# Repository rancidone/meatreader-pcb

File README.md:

# ESP32 Wireless Thermometer

## Overview
This project is a **custom, battery-powered ESP32-based wireless thermometer** designed for BBQ and probe-based temperature monitoring.

The goal is to build a **robust, safe, and manufacturable device** suitable for real-world use, not a development board or a proof-of-concept. The design prioritizes reliability, serviceability, and clear engineering tradeoffs over extreme miniaturization or feature creep.

---

## Project Goals
- Battery-powered operation using a single-cell Li-ion / LiPo battery
- 24+ hour runtime under typical use
- In-place battery charging via USB-C (power only)
- Wireless connectivity (Wi-Fi required, BLE optional)
- OTA firmware update capability
- Support for multiple external thermistor probes
- Safe hot-plugging of all external connectors
- Outdoor and kitchen-safe electrical robustness
- Aluminum enclosure compatibility with minimal machining tools
- Low-cost, reproducible manufacturing
- Friendly to both SMT assembly and hand soldering

---

## Design Philosophy
This project is guided by the following principles:

- **Safety first**  
  All external connections must tolerate hot-plugging, static discharge, and user error without damaging the device.

- **Manufacturable by design**  
  Components and footprints are selected with real-world assembly in mind, favoring widely available parts and avoiding unnecessary complexity.

- **Debuggable and understandable**  
  The design should be easy to inspect, measure, and troubleshoot without specialized equipment.

- **Incremental improvement**  
  Revisions build on known-good designs, preserving proven circuits while improving specific areas as needed.

---

## Non-Goals
The following are explicitly out of scope:
- USB data or USB-PD support
- Power-bank or device-charging functionality
- Ultra-miniaturized or wearable form factors
- Dev-board style layouts
- Feature-driven complexity that compromises reliability

---

## Repository Structure
This repository contains the hardware design files and supporting documentation for the project.

Typical contents include:
- KiCad schematics and PCB layouts
- Project-local symbol and footprint libraries
- Design notes and revision history
- Manufacturing and assembly references

Generated outputs (Gerbers, fabrication files, temporary caches) are not tracked unless explicitly required.

---

## Status
This repository contains an evolving hardware design with multiple revisions. Earlier revisions serve as validated references; newer revisions focus on improved power handling, manufacturability, and long-term reliability.

---

## License
This project is intended for personal, educational, and hobbyist use. Licensing details may be added as the design matures.

---

## Acknowledgements
This project draws on common, well-established embedded hardware design patterns and prioritizes practical engineering over novelty.

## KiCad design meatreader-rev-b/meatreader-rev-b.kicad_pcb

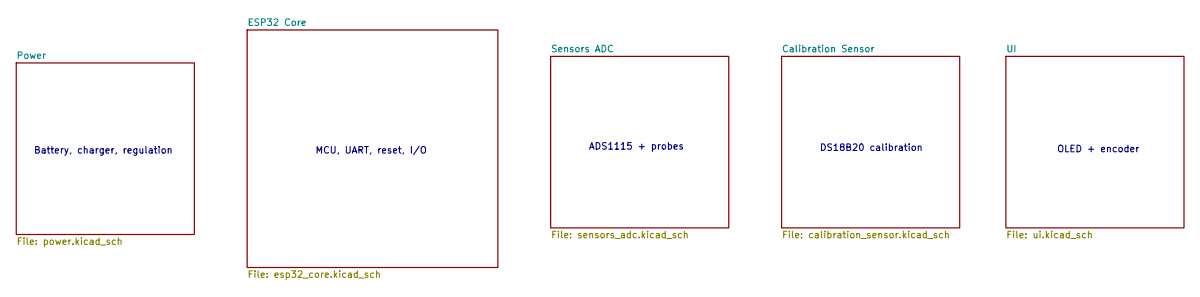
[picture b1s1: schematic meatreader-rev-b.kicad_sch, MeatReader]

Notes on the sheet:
MCU, UART, reset, I/O
ADS1115 + probes
OLED + encoder
Battery, charger, regulation
DS18B20 calibration

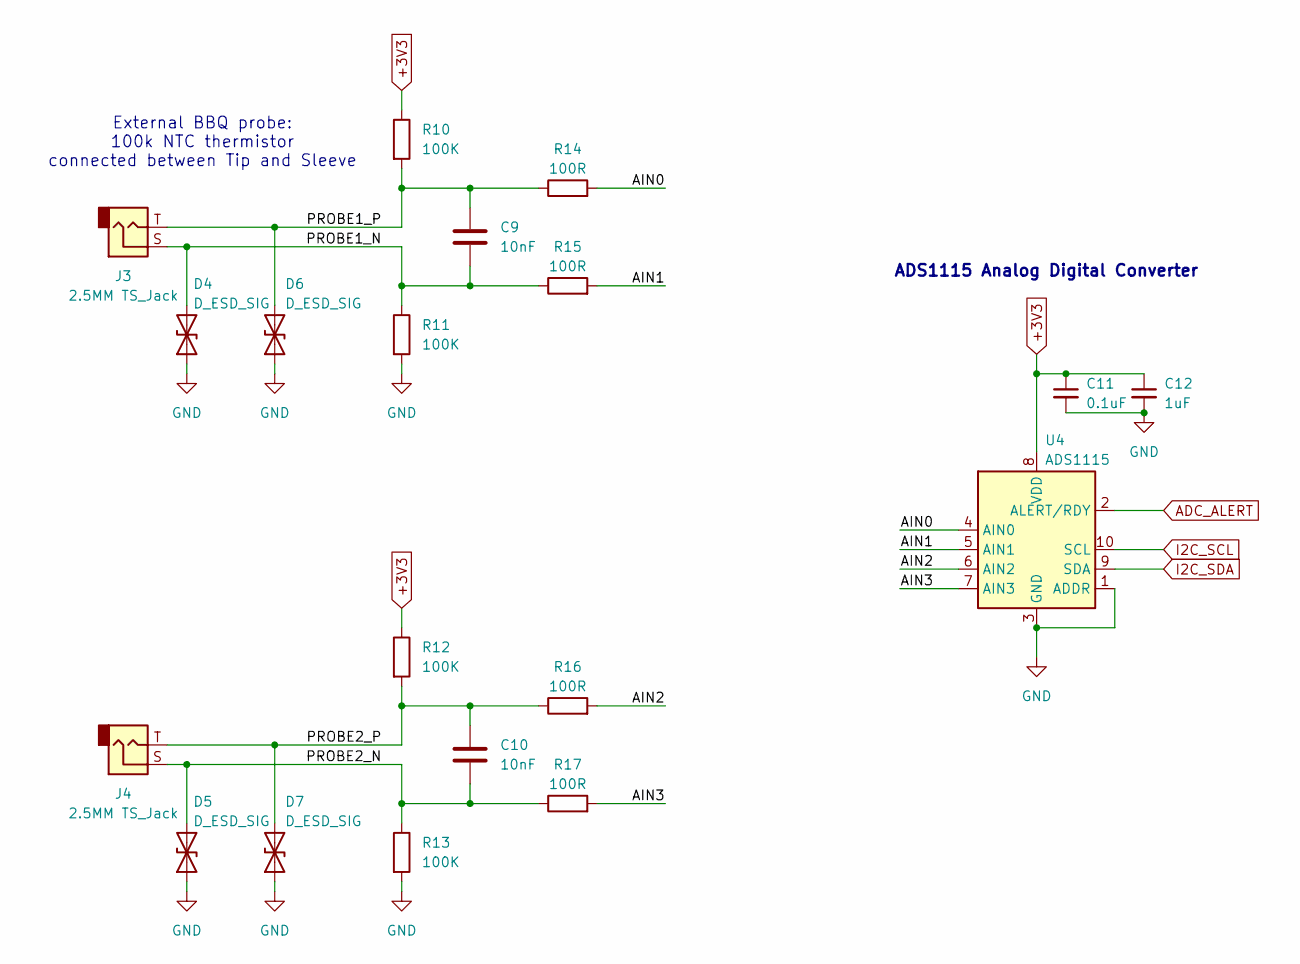
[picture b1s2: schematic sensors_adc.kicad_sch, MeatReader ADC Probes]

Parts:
C9, C10: 10nF; C_0603_1608Metric
C11: 0.1uF; C_0603_1608Metric
C12: 1uF; C_0603_1608Metric
D4, D5: D_ESD_SIG; D_0402_1005Metric; LCSC C20615778
D6, D7: D_ESD_SIG; D_0402_1005Metric
J3, J4: 2.5MM TS_Jack; Jack_2.5MM_PJ210B_TS; JLC_3DModel_Q 9e36057968d7478ca8658f227985305d
R10, R11, R12, R13: 100K; R_0603_1608Metric
R14, R15, R16, R17: 100R; R_0603_1608Metric
U4: ADS1115; TSSOP-10_3x3mm_P0.5mm

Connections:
+3V3: C11.1, C12.1, R10.1, R12.1, U4.8 (VDD); also elsewhere on the board
/Sensors ADC/AIN0: R14.2, U4.4 (AIN0)
/Sensors ADC/AIN1: R15.2, U4.5 (AIN1)
/Sensors ADC/AIN2: R16.2, U4.6 (AIN2)
/Sensors ADC/AIN3: R17.2, U4.7 (AIN3)
/Sensors ADC/PROBE1_N: C9.2, D4.2 (A2), J3.S, R11.1, R15.1
/Sensors ADC/PROBE1_P: C9.1, D6.2 (A2), J3.T, R10.2, R14.1
/Sensors ADC/PROBE2_N: C10.2, D5.2 (A2), J4.S, R13.1, R17.1
/Sensors ADC/PROBE2_P: C10.1, D7.2 (A2), J4.T, R12.2, R16.1
ADC_ALERT: U4.2 (ALERT/RDY); also elsewhere on the board
GND: C11.2, C12.2, D4.1 (A1), D5.1 (A1), D6.1 (A1), D7.1 (A1), R11.2, R13.2, U4.1 (ADDR), U4.3 (GND); also elsewhere on the board
I2C_SCL: U4.10 (SCL); also elsewhere on the board
I2C_SDA: U4.9 (SDA); also elsewhere on the board

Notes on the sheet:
External BBQ probe: 100k NTC thermistor connected between Tip and Sleeve
ADS1115 Analog Digital Converter

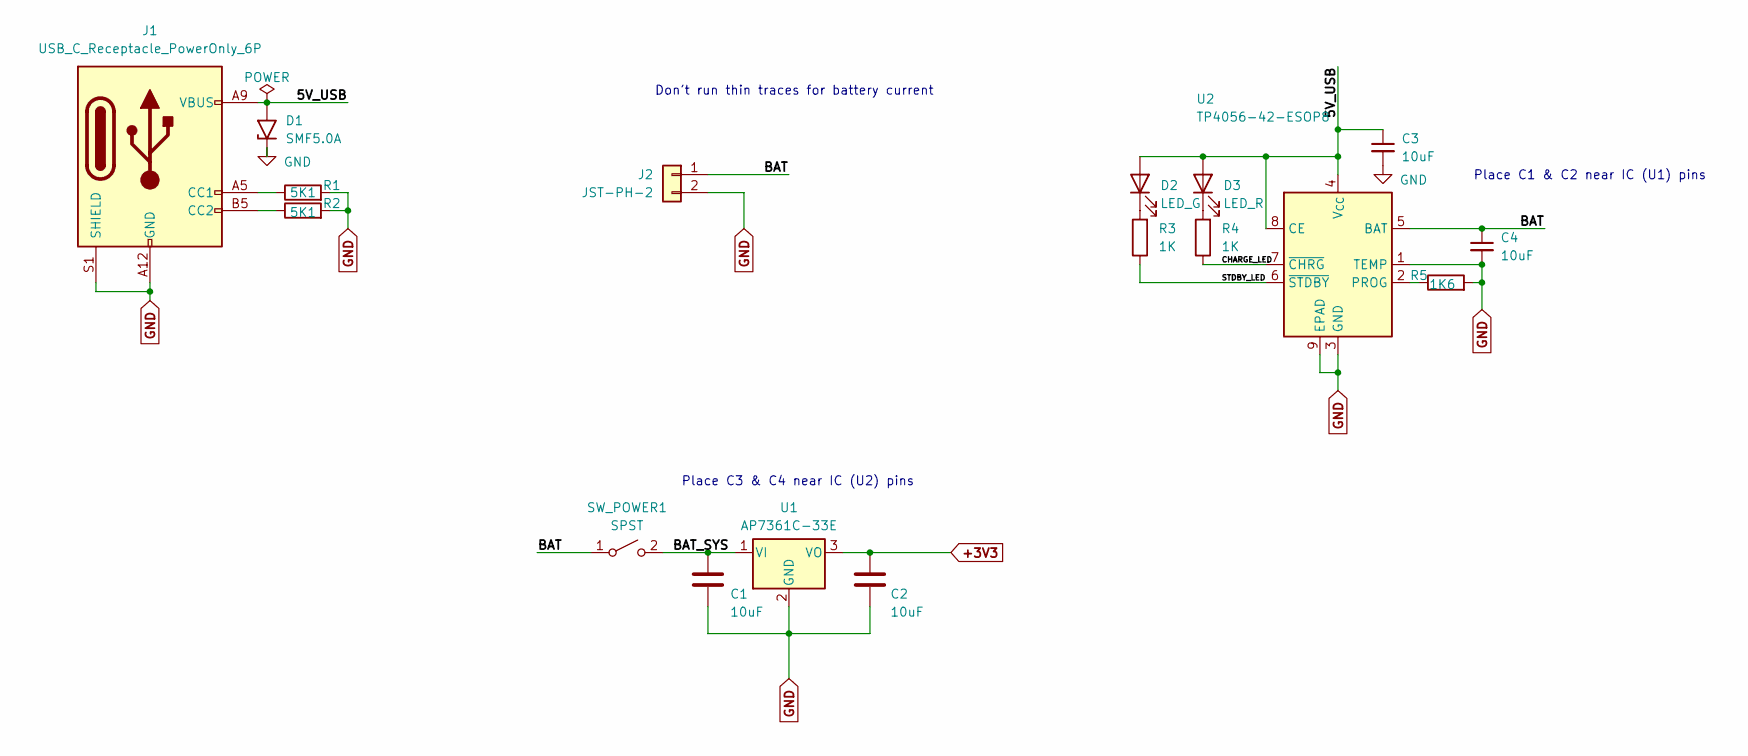
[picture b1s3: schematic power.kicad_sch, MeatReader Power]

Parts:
C1, C2, C3, C4: 10uF; C_0805_2012Metric
D1: SMF5.0A; D_SMF; LCSC C19077497
D2: LED_G; LED_D3.0mm
D3: LED_R; LED_D3.0mm
J1: USB_C_Receptacle_PowerOnly_6P; USB_C_Receptacle_HRO_TYPE-C-31-M-12
J2: JST-PH-2; JST_PH_B2B-PH-K_1x02_P2.00mm_Vertical
R1, R2: 5K1; R_0402_1005Metric
R3, R4: 1K; R_0402_1005Metric; LCSC C11702
R5: 1K6; R_0402_1005Metric
SW_POWER1: SPST; PinHeader_1x02_P2.54mm_Vertical
U1: AP7361C-33E; SOT-223-3_TabPin2
U2: TP4056-42-ESOP8; SOIC-8-1EP_3.9x4.9mm_P1.27mm_EP2.41x3.3mm

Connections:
+3V3: C2.1, U1.3 (VO); also elsewhere on the board
/Power/5V_USB: C3.1, D1.2 (A2), D2.2 (A), D3.2 (A), J1.A9 (VBUS), J1.B9 (VBUS), U2.4 (V_{CC}), U2.8 (CE)
/Power/BAT: C4.1, J2.1, SW_POWER1.1 (A), U2.5 (BAT)
/Power/BAT_SYS: C1.1, SW_POWER1.2 (B), U1.1 (VI)
/Power/CHARGE_LED: R4.1, U2.7 (~CHRG)
/Power/STDBY_LED: R3.1, U2.6 (~STDBY)
GND: C1.2, C2.2, C3.2, C4.2, D1.1 (A1), J1.A12 (GND), J1.B12 (GND), J1.S1 (SHIELD), J2.2, R1.2, R2.2, R5.2, U1.2 (GND), U2.1 (TEMP), U2.3 (GND), U2.9 (EPAD); also elsewhere on the board
unnamed: D2.1 (K), R3.2
unnamed: D3.1 (K), R4.2
unnamed: J1.A5 (CC1), R1.1
unnamed: J1.B5 (CC2), R2.1
unnamed: R5.1, U2.2 (PROG)

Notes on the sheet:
Don't run thin traces for battery current
Place C1 & C2 near IC (U1) pins
Place C3 & C4 near IC (U2) pins

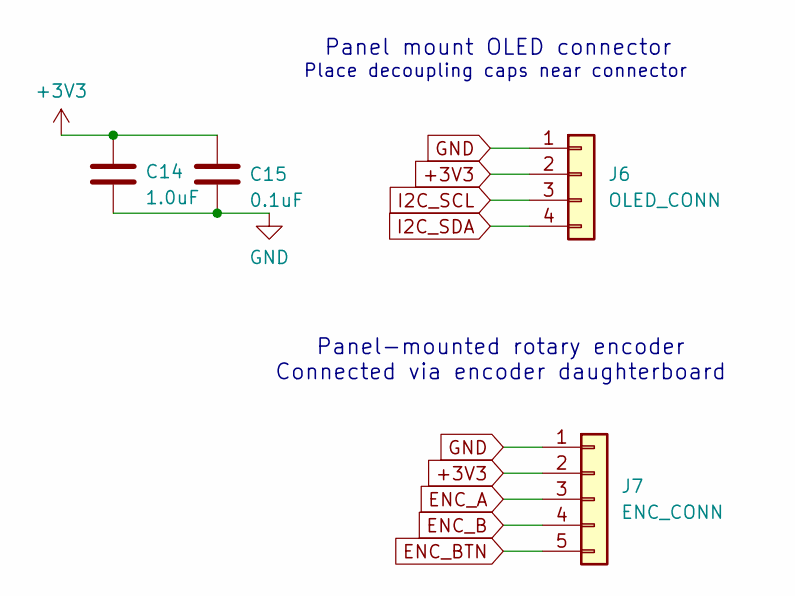
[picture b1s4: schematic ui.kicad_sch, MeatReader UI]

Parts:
C14: 1.0uF; C_0603_1608Metric
C15: 0.1uF; C_0603_1608Metric
J6: OLED_CONN; JST_XH_B4B-XH-AM_1x04_P2.50mm_Vertical
J7: ENC_CONN; JST_XH_B5B-XH-AM_1x05_P2.50mm_Vertical

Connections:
+3V3: C14.1, C15.1, J6.2, J7.2; also elsewhere on the board
ENC_A: J7.3; also elsewhere on the board
ENC_B: J7.4; also elsewhere on the board
ENC_BTN: J7.5; also elsewhere on the board
GND: C14.2, C15.2, J6.1, J7.1; also elsewhere on the board
I2C_SCL: J6.3; also elsewhere on the board
I2C_SDA: J6.4; also elsewhere on the board

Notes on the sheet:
Panel-mounted rotary encoder Connected via encoder daughterboard
Place decoupling caps near connector
Panel mount OLED connector

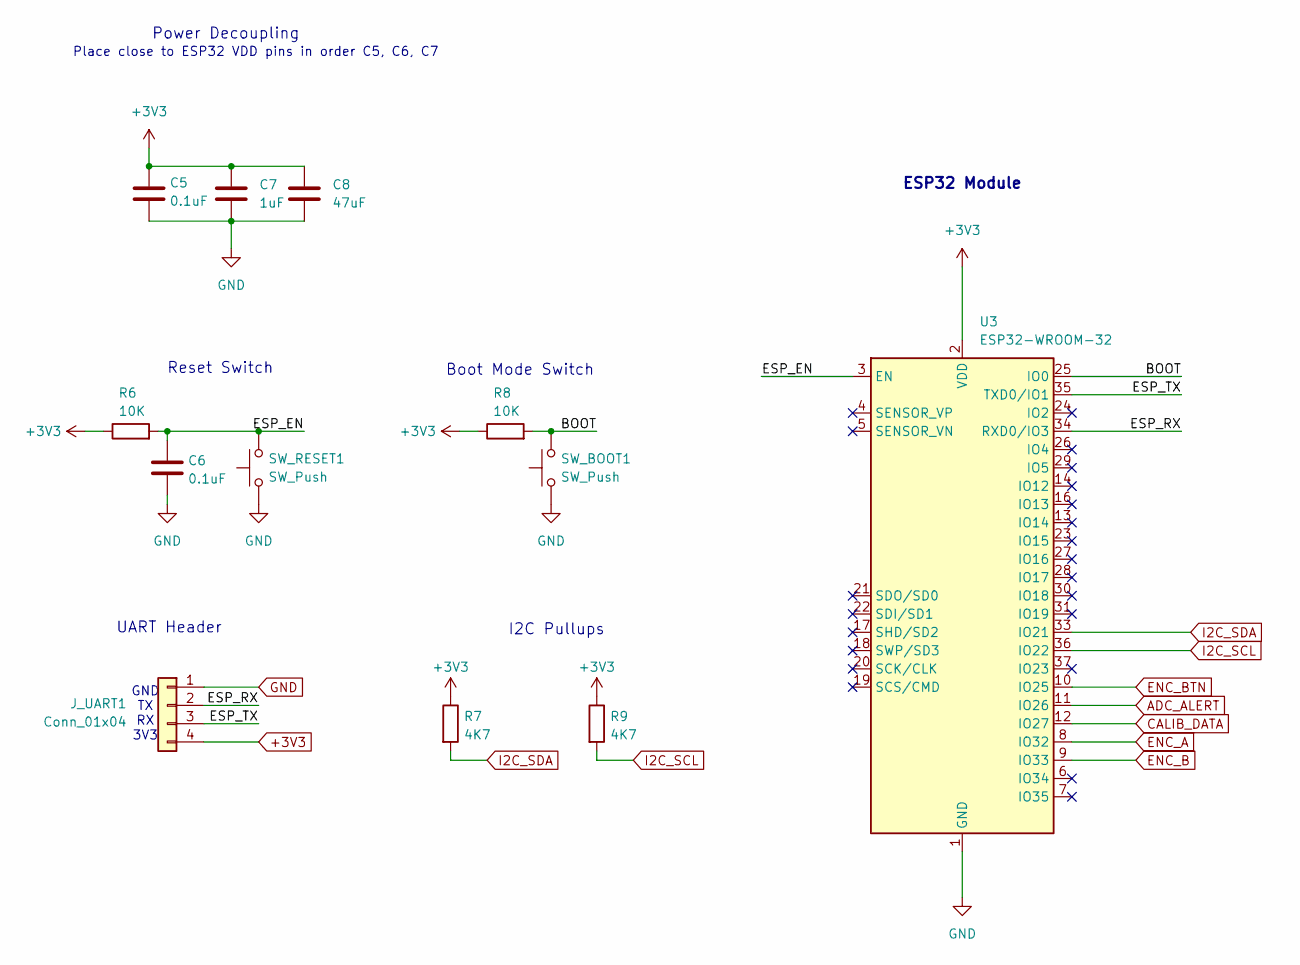
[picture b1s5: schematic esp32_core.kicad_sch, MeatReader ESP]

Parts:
C5, C6: 0.1uF; C_0603_1608Metric
C7: 1uF; C_0603_1608Metric
C8: 47uF; C_0805_2012Metric
J_UART1: Conn_01x04; PinHeader_1x04_P2.54mm_Vertical
R6, R8: 10K; R_0603_1608Metric
R7, R9: 4K7; R_0603_1608Metric
SW_BOOT1: SW_Push; Test_01x02
SW_RESET1: SW_Push; SW_PUSH_6mm
U3: ESP32-WROOM-32; ESP32-WROOM-32_NoThermals

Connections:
+3V3: C5.1, C7.1, C8.1, J_UART1.4, R6.1, R7.1, R8.1, R9.1, U3.2 (VDD); also elsewhere on the board
/ESP32 Core/BOOT: R8.2, SW_BOOT1.2, U3.25 (IO0)
/ESP32 Core/ESP_EN: C6.1, R6.2, SW_RESET1.2, U3.3 (EN)
/ESP32 Core/ESP_RX: J_UART1.2, U3.34 (RXD0/IO3)
/ESP32 Core/ESP_TX: J_UART1.3, U3.35 (TXD0/IO1)
ADC_ALERT: U3.11 (IO26); also elsewhere on the board
CALIB_DATA: U3.12 (IO27); also elsewhere on the board
ENC_A: U3.8 (IO32); also elsewhere on the board
ENC_B: U3.9 (IO33); also elsewhere on the board
ENC_BTN: U3.10 (IO25); also elsewhere on the board
GND: C5.2, C6.2, C7.2, C8.2, J_UART1.1, SW_BOOT1.1, SW_RESET1.1, U3.1 (GND), U3.15 (GND), U3.38 (GND), U3.39 (GND); also elsewhere on the board
I2C_SCL: R9.2, U3.36 (IO22); also elsewhere on the board
I2C_SDA: R7.2, U3.33 (IO21); also elsewhere on the board

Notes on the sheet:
GND TX RX 3V3
I2C Pullups
UART Header
Power Decoupling
Place close to ESP32 VDD pins in order C5, C6, C7
Reset Switch
Boot Mode Switch
ESP32 Module

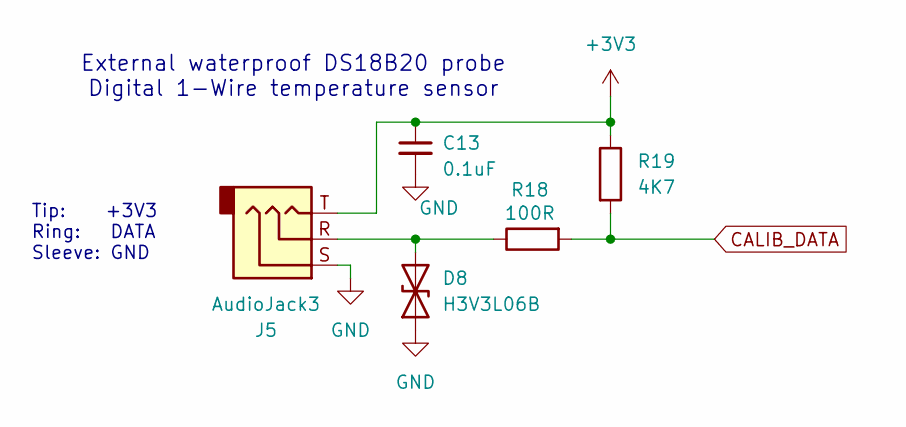
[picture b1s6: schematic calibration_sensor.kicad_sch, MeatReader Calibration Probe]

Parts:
C13: 0.1uF; C_0603_1608Metric
D8: H3V3L06B; D_0402_1005Metric
J5: AudioJack3; PJ-320A_TRS
R18: 100R; R_0603_1608Metric
R19: 4K7; R_0603_1608Metric

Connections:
+3V3: C13.1, J5.T, R19.1; also elsewhere on the board
CALIB_DATA: R18.2, R19.2; also elsewhere on the board
GND: C13.2, D8.1 (A1), J5.S; also elsewhere on the board
unnamed: D8.2 (A2), J5.R, R18.1

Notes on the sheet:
External waterproof DS18B20 probe Digital 1-Wire temperature sensor
Tip: +3V3 Ring: DATA Sleeve: GND

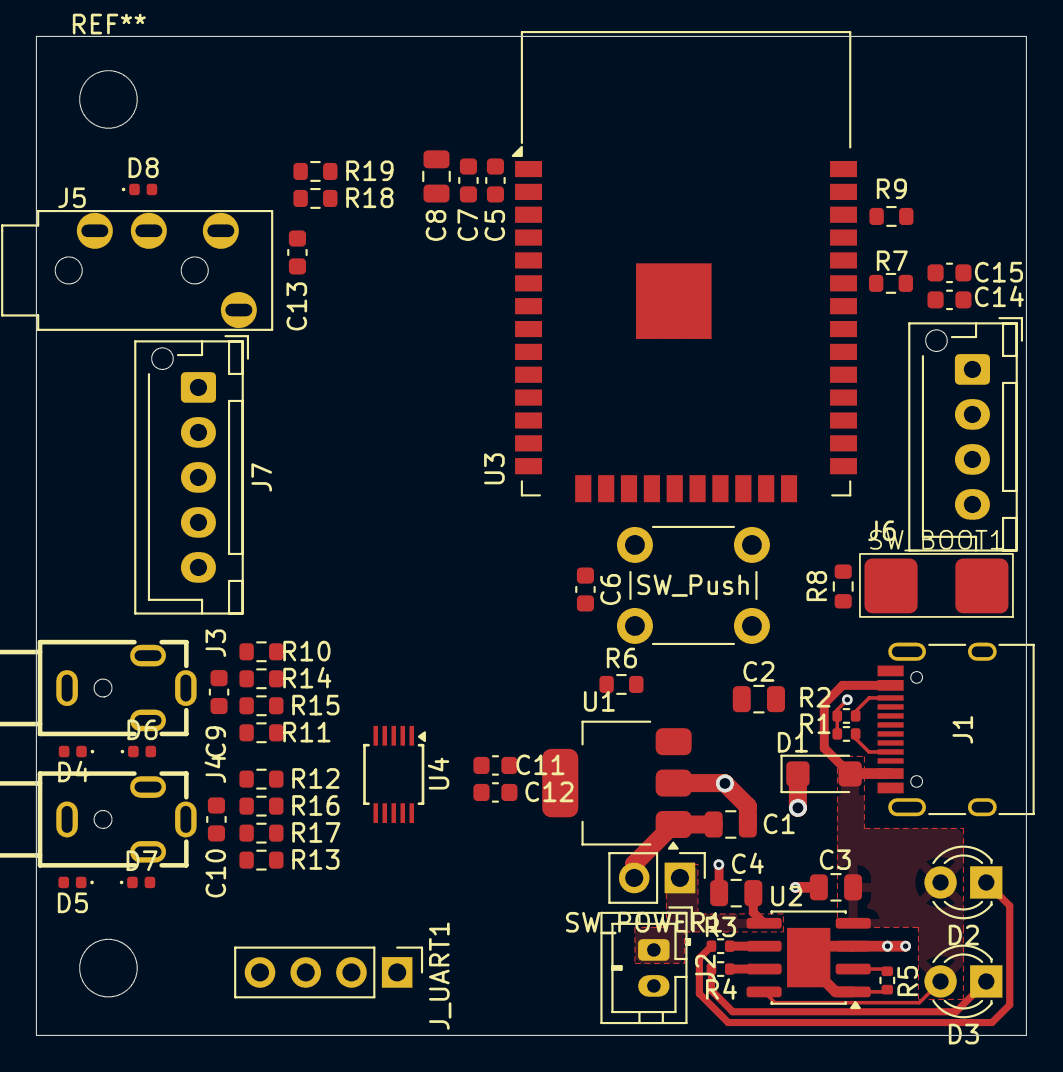
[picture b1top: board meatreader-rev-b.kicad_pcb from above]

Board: 2 copper layers, 55.0 x 55.5 mm, 57 parts (0 on the bottom side), 32 nets.

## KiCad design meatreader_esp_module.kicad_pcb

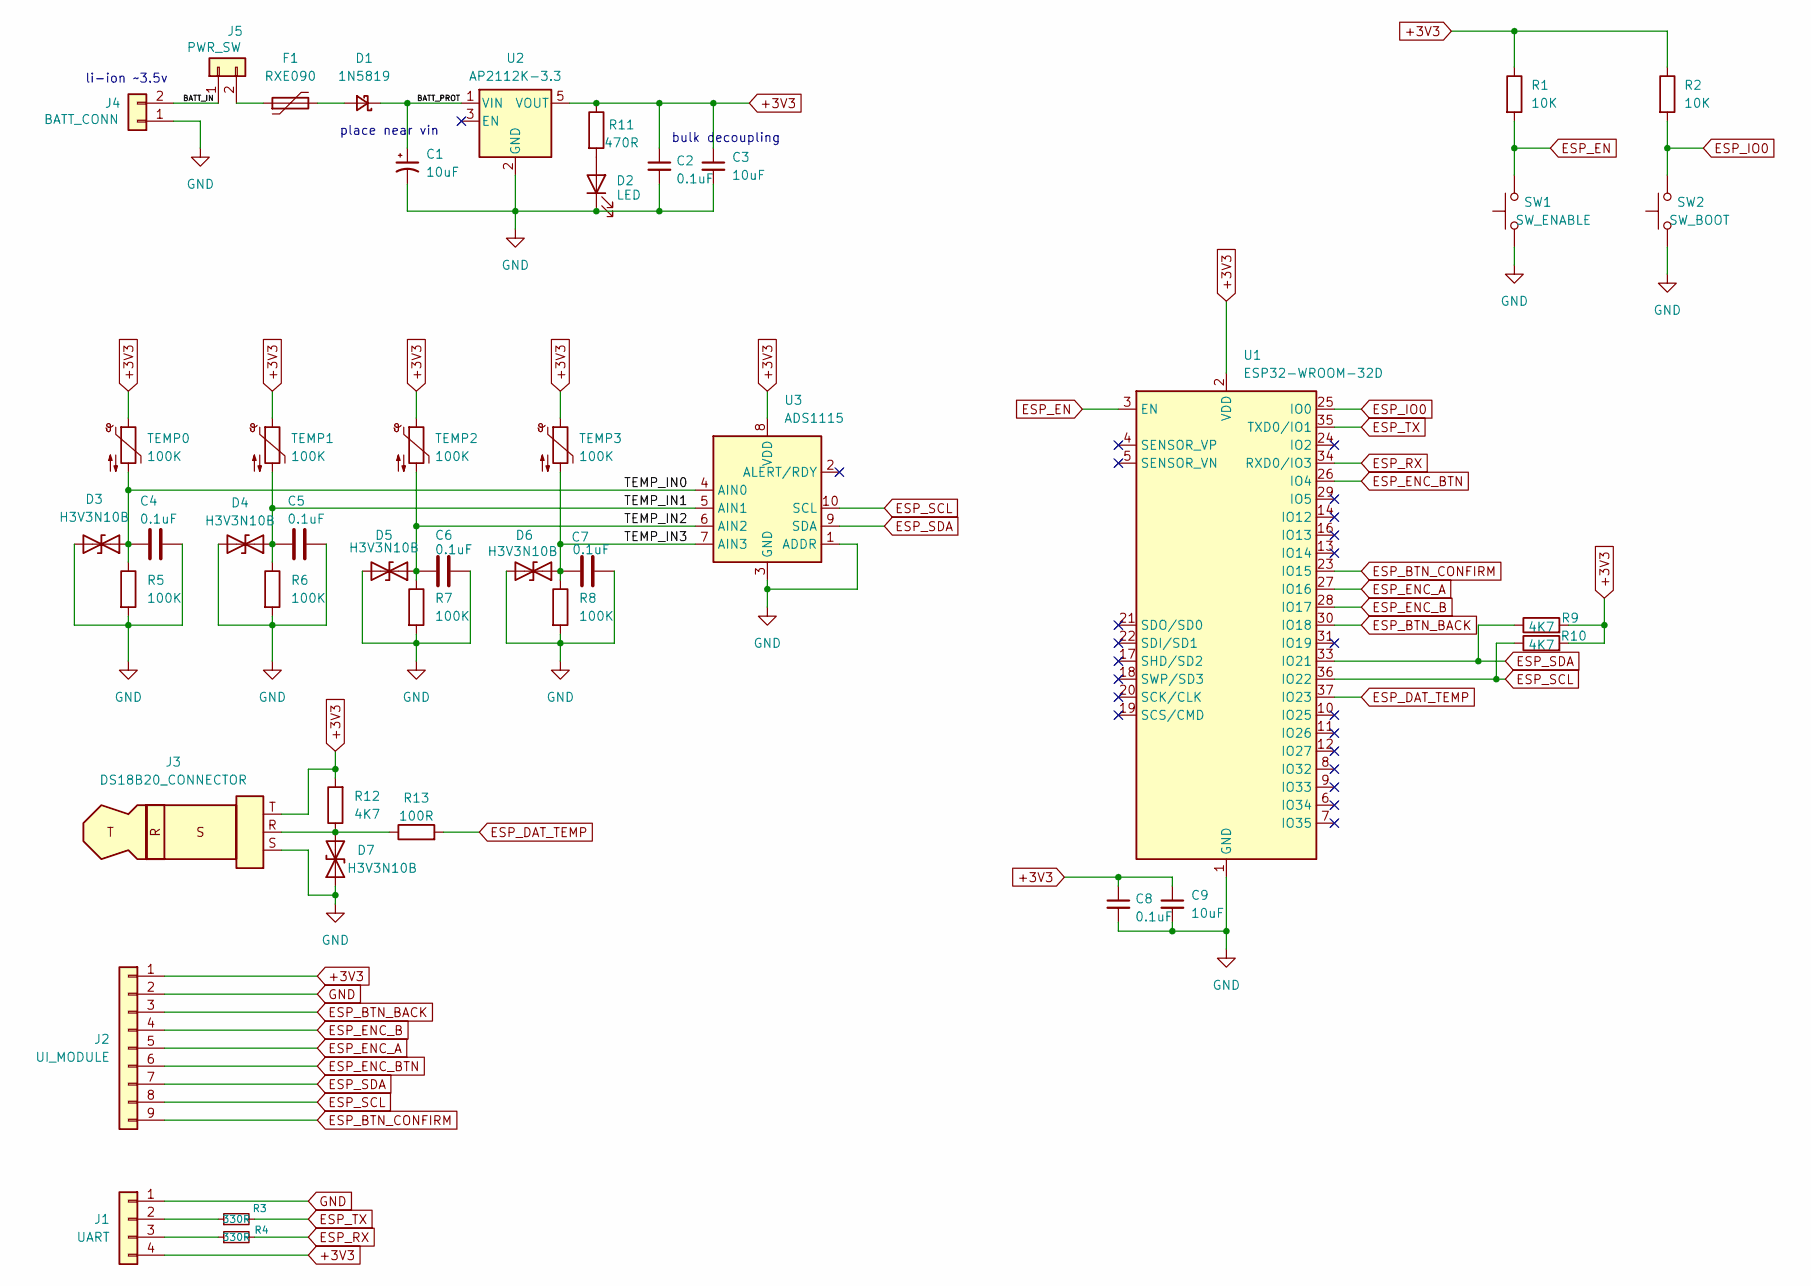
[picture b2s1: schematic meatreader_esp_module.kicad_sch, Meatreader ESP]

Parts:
C1, C9: 10uF; CP_Radial_D5.0mm_P2.50mm
C2, C4, C5, C6, C7, C8: 0.1uF; C_0603_1608Metric; LCSC C14663
C3: 10uF; C_0603_1608Metric; LCSC C19702
D1: 1N5819; D_DO-41_SOD81_P10.16mm_Horizontal
D2: LED; LED_0603_1608Metric; LCSC C2286
D3, D4, D5, D6, D7: H3V3N10B; D_SOD-882; LCSC C20617909
F1: RXE090; C_Axial_L5.1mm_D3.1mm_P7.50mm_Horizontal
J1: UART; PinHeader_1x04_P2.54mm_Vertical
J2: UI_MODULE; PinHeader_1x09_P2.54mm_Vertical
J3: DS18B20_CONNECTOR; PJ-320A_TRS
J4: BATT_CONN; JST_PH_B2B-PH-K_1x02_P2.00mm_Vertical
J5: PWR_SW; PinHeader_1x02_P2.54mm_Vertical
R1: 10K; R_0603_1608Metric; LCSC C25804
R2: 10K; R_Axial_DIN0207_L6.3mm_D2.5mm_P7.62mm_Horizontal
R3, R4: 330R; R_Axial_DIN0207_L6.3mm_D2.5mm_P7.62mm_Horizontal
R5, R6, R7, R8: 100K; R_Axial_DIN0207_L6.3mm_D2.5mm_P7.62mm_Horizontal
R9, R10, R12: 4K7; R_Axial_DIN0207_L6.3mm_D2.5mm_P7.62mm_Horizontal
R11: 470R; R_Axial_DIN0207_L6.3mm_D2.5mm_P7.62mm_Horizontal
R13: 100R; R_Axial_DIN0207_L6.3mm_D2.5mm_P7.62mm_Horizontal
SW1: SW_ENABLE; SW_PUSH_6mm_H5mm
SW2: SW_BOOT; SW_PUSH_6mm_H5mm
TEMP0, TEMP1, TEMP2, TEMP3: 100K; Jack_2.5MM_PJ210B; JLC_3DModel_Q 9e36057968d7478ca8658f227985305d
U1: ESP32-WROOM-32D; ESP32_D0WD
U2: AP2112K-3.3; SOT-23-5; LCSC C23380830
U3: ADS1115; TSSOP-10_3x3mm_P0.5mm; LCSC C37593

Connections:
+3V3: C2.1, C3.1, C8.1, C9.1, J1.4 (VCC), J2.1, J3.T, R1.1, R2.1, R9.2, R10.2, R11.1, R12.2, TEMP0.1, TEMP1.1, TEMP2.1, TEMP3.1, U1.2 (VDD), U2.5 (VOUT), U3.8 (VDD)
/BATT_IN: J4.2, J5.1
/BATT_PROT: C1.1, D1.1 (K), U2.1 (VIN)
/TEMP_IN0: C4.1, D3.1 (A1), R5.1, TEMP0.2, U3.4 (AIN0)
/TEMP_IN1: C5.1, D4.1 (A1), R6.1, TEMP1.2, U3.5 (AIN1)
/TEMP_IN2: C6.1, D5.1 (A1), R7.1, TEMP2.2, U3.6 (AIN2)
/TEMP_IN3: C7.1, D6.1 (A1), R8.1, TEMP3.2, U3.7 (AIN3)
ESP_BTN_BACK: J2.3, U1.30 (IO18)
ESP_BTN_CONFIRM: J2.9, U1.23 (IO15)
ESP_DAT_TEMP: R13.2, U1.37 (IO23)
ESP_EN: R1.2, SW1.2, U1.3 (EN)
ESP_ENC_A: J2.5, U1.27 (IO16)
ESP_ENC_B: J2.4, U1.28 (IO17)
ESP_ENC_BTN: J2.6, U1.26 (IO4)
ESP_IO0: R2.2, SW2.2, U1.25 (IO0)
ESP_RX: R4.2, U1.34 (RXD0/IO3)
ESP_SCL: J2.8, R10.1, U1.36 (IO22), U3.10 (SCL)
ESP_SDA: J2.7, R9.1, U1.33 (IO21), U3.9 (SDA)
ESP_TX: R3.2, U1.35 (TXD0/IO1)
GND: C1.2, C2.2, C3.2, C4.2, C5.2, C6.2, C7.2, C8.2, C9.2, D2.1 (K), D3.2 (A2), D4.2 (A2), D5.2 (A2), D6.2 (A2), D7.1 (A1), J1.1 (GND), J2.2, J3.S, J4.1, R5.2, R6.2, R7.2, R8.2, SW1.1, SW2.1, U1.1 (GND), U1.15 (GND), U1.38 (GND), U1.39 (GND), U2.2 (GND), U3.1 (ADDR), U3.3 (GND)
unnamed: D1.2 (A), F1.2
unnamed: D2.2 (A), R11.2
unnamed: D7.2 (A2), J3.R, R12.1, R13.1
unnamed: J1.3 (RX), R4.1
unnamed: J1.2 (TX), R3.1
unnamed: F1.1, J5.2

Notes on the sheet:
place near vin
li-ion ~3.5v
bulk decoupling

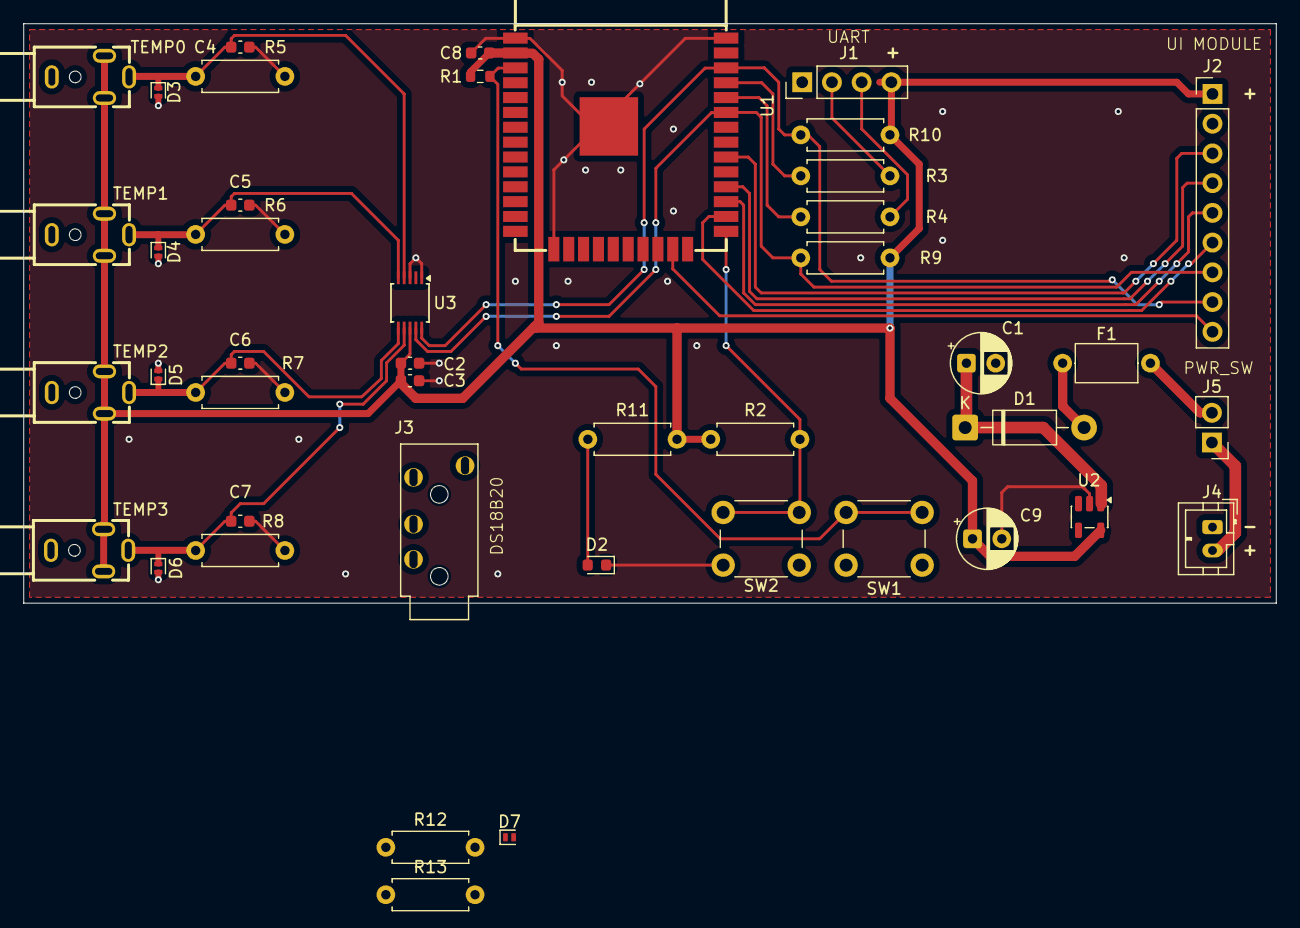
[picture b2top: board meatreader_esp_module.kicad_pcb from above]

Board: 2 copper layers, 107.0 x 49.5 mm, 44 parts (0 on the bottom side), 26 nets.

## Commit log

2026-01-10 Initial commit, legacy version. Incomplete.
2026-01-10 Move rev-a to a folder, create rev-b project
2026-01-15 Power and ESP core
2026-01-17 rev-b initial commit
2026-01-22 start routing
